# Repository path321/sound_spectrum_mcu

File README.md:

# Sound Analyzer

STM32-powered board for analyzing sound input from MEMS microphones, designed as an open-source, hands-on introduction to DSP on ARM Cortex-M4 processors.

## Table of Contents

1. [About the Project](#about-the-project)
1. [Project Status](#project-status)
1. [Getting Started](#getting-started)
	1. [Getting the Source](#getting-the-source)
	1. [Usage](#usage)
	1. [Versioning](#versioning)
1. [How to get help](#how-to-get-help)
1. [License](#license)

## About the Project

It uses the CMSIS-DSP library to handle computationally intensive tasks, while a companion PyQt-based Python script is used for plotting frequency-domain data data from PCB to host PC. 

The goal is to demonstrate the full pipeline of audio signal acquisition and transformation, from raw time-domain data to frequency-domain analysis

The PCB intentionally exposes additional unused pins, allowing users to extend functionality and experiment beyond the core features

_1kHz sine_

Front                      |  Back
:-------------------------:|:-------------------------:
  |  

**[Back to top](#table-of-contents)**

## Project Status

In progress, working version availabe in `main` branch

Full STM32CubeIDE project is hosted here, with .elf and .bin files ready inside `code/sound_analyzer_v1/Debug` folder

As for python script, both source `plot_graph.py` and executable `plot_graph.exe` are available, with executable tested only for Windows platform

**[Back to top](#table-of-contents)**

## Getting Started

For application usage, no extra programm shall be installed , other than downloading the executable plot_graph.exe

For developer usage, STM32CubeIDE + STM32CubeMX shall be installed, as described [here](https://wiki.st.com/stm32mcu/wiki/STM32StepByStep:Step1_Tools_installation)

In addition, Python >=3.9 shall be installed from [here](https://www.python.org/downloads/), with the following Python libraries also installed :
- Numpy
- PySide6
- pyqtgraph
- Pyserial

PCB files are located on `pcb/` folder, while device files can be found on `code/sound_analyzer_v1/` and plot files on `code/plot_graph/`

### Getting the Source

This project is [hosted on GitHub](https://github.com/path321/sound_spectrum_mcu). You can clone this project directly using this command:

```
https://github.com/path321/sound_spectrum_mcu.git
```

### Usage

1) Connect the board via USB to your host PC. Make sure that no other STM32-based USB is connected to PC

2) Unzip plot_graph.zip Double click on plot_graph.exe

3) If you want to stop the live graph, check on the Button on the top right end of the GUI window

### Versioning

This project uses [Semantic Versioning](http://semver.org/). For a list of available versions, see the [repository tag list](https://github.com/path321/sound_spectrum_mcu/tags).

**[Back to top](#table-of-contents)**

## How to Get Help

Please create a new issue on

```https://github.com/path321/sound_spectrum_mcu/issues```

**[Back to top](#table-of-contents)**

## License

This project is licensed under the MIT License - see [LICENSE.md](LICENSE.md) file for details.

**[Back to top](#table-of-contents)**

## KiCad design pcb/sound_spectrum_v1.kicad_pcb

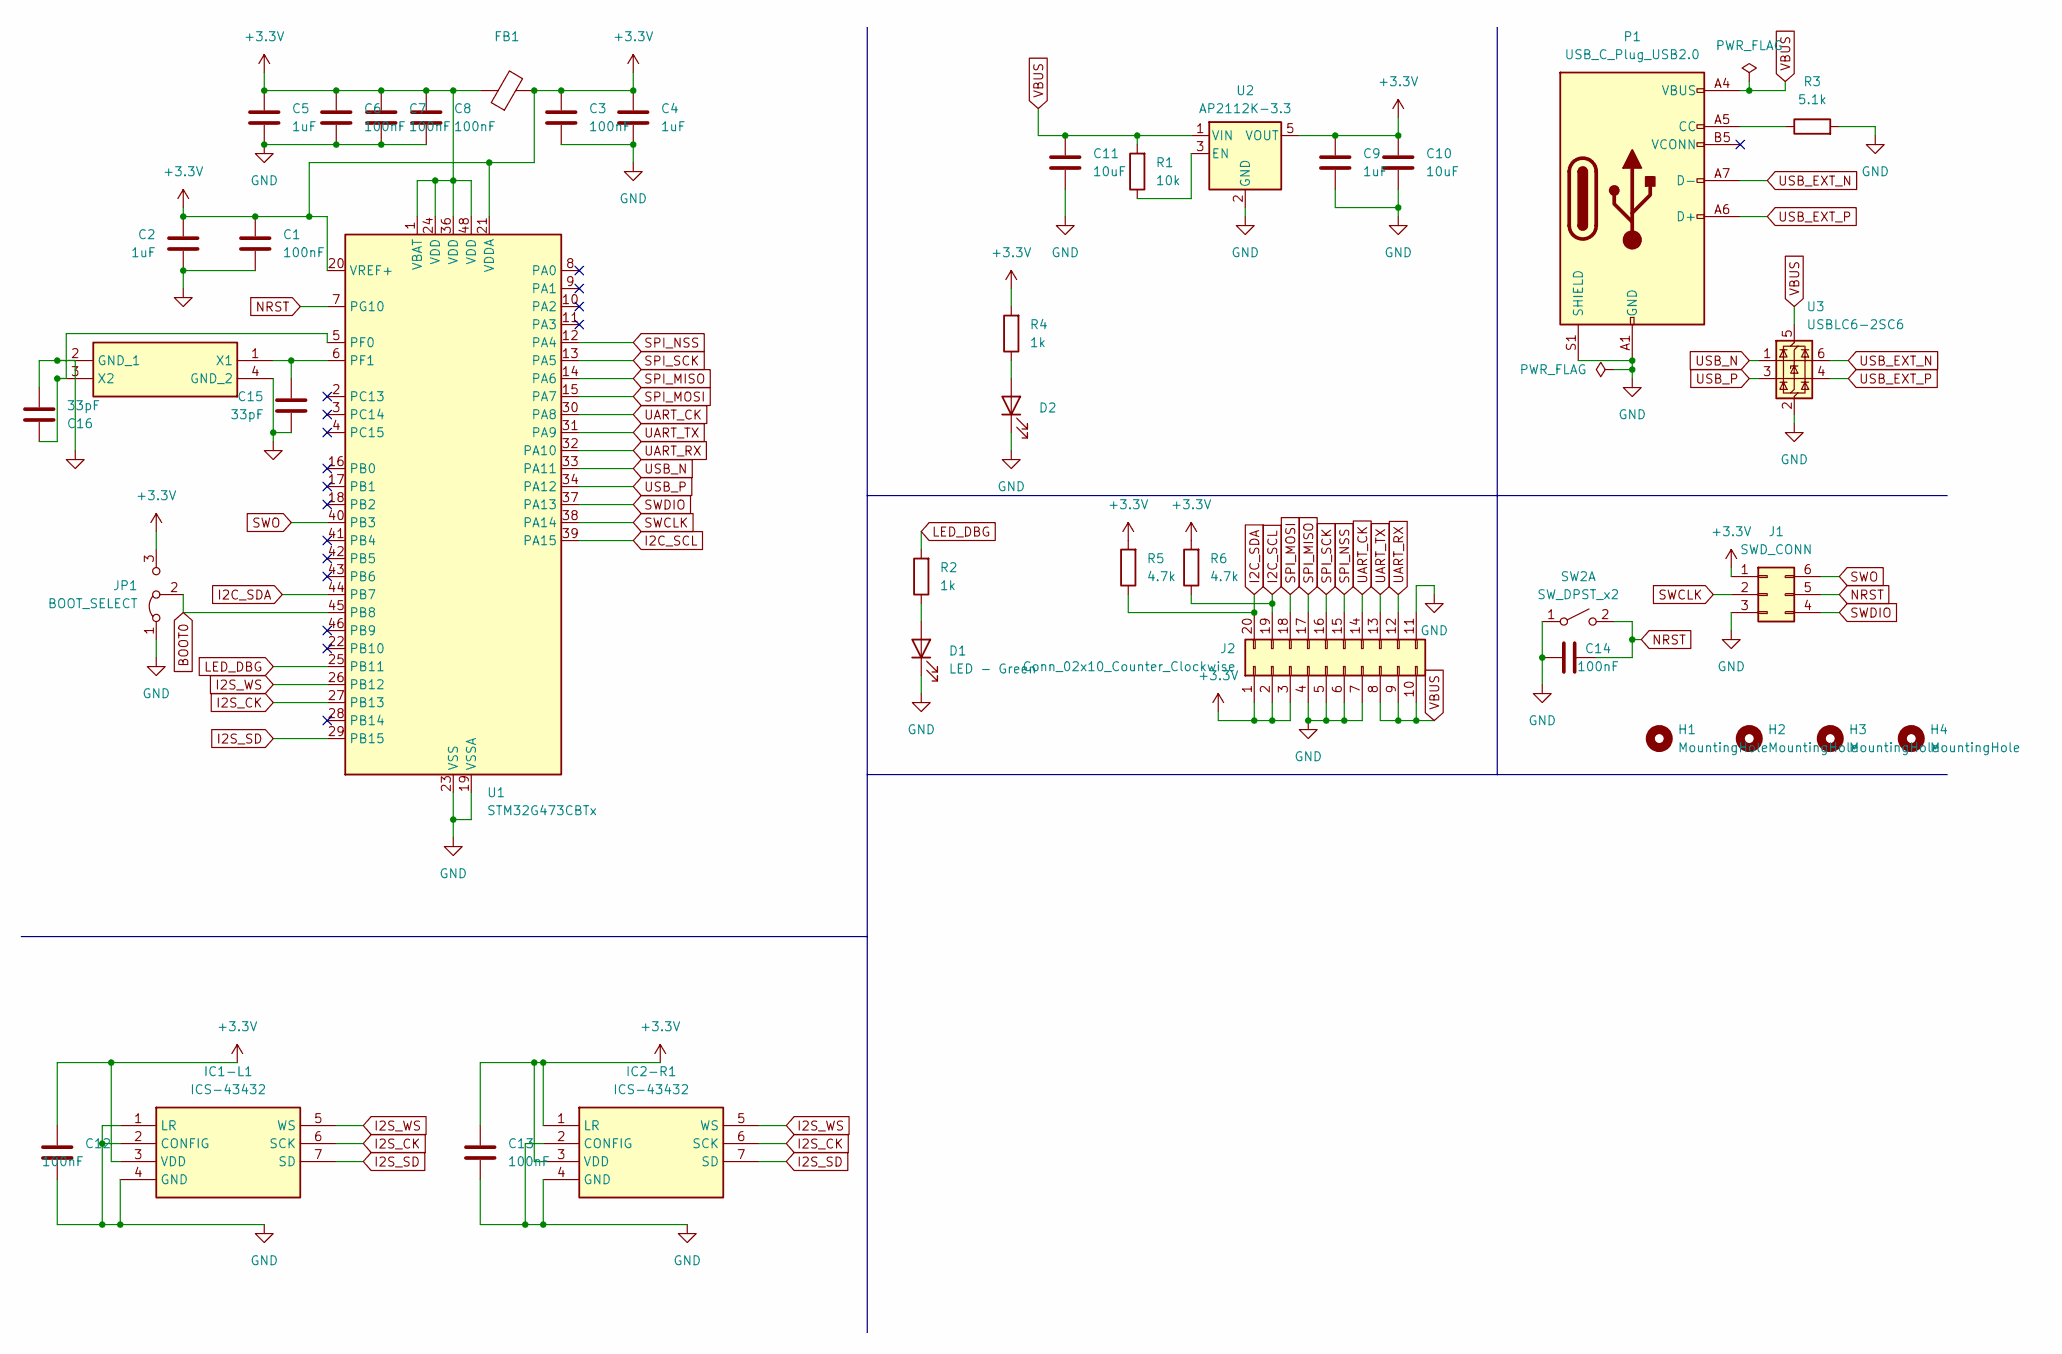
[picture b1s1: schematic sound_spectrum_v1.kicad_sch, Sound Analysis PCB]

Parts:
C1, C3, C6, C7, C8, C12, C13, C14: 100nF; C_0805_2012Metric_Pad1.18x1.45mm_HandSolder; Manufacturer_Part_Number 581-KGM21NR71E104KM
C2, C4, C5, C9: 1uF; C_0805_2012Metric_Pad1.18x1.45mm_HandSolder; Manufacturer_Part_Number 80-C0805C105Z4VAC
C10, C11: 10uF; C_0805_2012Metric_Pad1.18x1.45mm_HandSolder; Manufacturer_Part_Number 81-GRM21BR61C106KE15
C15, C16: 33pF; C_0805_2012Metric_Pad1.18x1.45mm_HandSolder; Manufacturer_Part_Number 80-C0805C105Z4VAC
D1: LED - Green; LED_0805_2012Metric_Pad1.15x1.40mm_HandSolder; Manufacturer_Part_Number C171KGKT
D2: LED - Red; LED_0805_2012Metric_Pad1.15x1.40mm_HandSolder; Manufacturer_Part_Number CMDA5AR7D1S
FB1: L_0805_2012Metric_Pad1.05x1.20mm_HandSolder; Manufacturer_Part_Number ASMPH-0805-4R7M-T
H1, H2, H3, H4: MountingHole; MountingHole_3.2mm_M3_DIN965
IC1-L1, IC2-R1: ICS-43432; ICS43432; Manufacturer_Part_Number ICS-43432; Mouser Part Number 410-ICS-43432
J1: SWD_CONN; PinHeader_2x03_P2.54mm_Vertical; Manufacturer_Part_Number 10129381-906004BLF
J2: Conn_02x10_Counter_Clockwise; PinHeader_2x10_P2.54mm_Vertical; Manufacturer_Part_Number 77313-818-20LF
JP1: BOOT_SELECT; SolderJumper-3_P1.3mm_Bridged2Bar12_Pad1.0x1.5mm
P1: USB_C_Plug_USB2.0; USB_C_Receptacle_GCT_USB4105-xx-A_16P_TopMnt_Horizontal; Manufacturer_Part_Number USB4085-GF-A
R1: 10k; R_0805_2012Metric_Pad1.20x1.40mm_HandSolder; Manufacturer_Part_Number 603-AC0805DR-0710KL
R2, R4: 1k; R_0805_2012Metric_Pad1.20x1.40mm_HandSolder; Manufacturer_Part_Number 603-AA0805FR-071KL
R3: 5.1k; R_0805_2012Metric_Pad1.20x1.40mm_HandSolder; Manufacturer_Part_Number CRCW08055K10JNEA
R5, R6: 4.7k; R_0805_2012Metric_Pad1.20x1.40mm_HandSolder; Manufacturer_Part_Number 603-RC0805FR-074K7L
SW2: SW_DPST_x2; SW_PUSH_6mm; Manufacturer_Part_Number TS04-66-55-BK-100-SMT-TR
U1: STM32G473CBTx; LQFP-48_7x7mm_P0.5mm; Manufacturer_Part_Number STM32G473CBT6
U2: AP2112K-3.3; SOT-23-5; Manufacturer_Part_Number AP2112K-3.3TRG1
U3: USBLC6-2SC6; SOT-23-6; Manufacturer_Part_Number USBLC6-2SC6
Y1: ABMM2-24.000MHZ-E2-T; ABMM2; Mouser Part Number 815-ABMM2-24-E2T

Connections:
+3.3V: C1.1, C2.1, C3.1, C4.1, C5.1, C6.1, C7.1, C8.1, C9.1, C10.1, C12.1, C13.1, FB1.1, FB1.2, IC1-L1.3 (VDD), IC2-R1.1 (LR), IC2-R1.3 (VDD), J1.1, J2.1, J2.2, J2.3, JP1.3 (B), R4.2, R5.2, R6.2, U1.1 (VBAT), U1.20 (VREF+), U1.21 (VDDA), U1.24 (VDD), U1.36 (VDD), U1.48 (VDD), U2.5 (VOUT)
BOOT0: JP1.2 (C), U1.45 (PB8)
GND: C1.2, C2.2, C3.2, C4.2, C5.2, C6.2, C7.2, C8.2, C9.2, C10.2, C11.2, C12.2, C13.2, C14.1, C15.2, C16.2, D1.1 (K), D2.1 (K), IC1-L1.1 (LR), IC1-L1.2 (CONFIG), IC1-L1.4 (GND), IC2-R1.2 (CONFIG), IC2-R1.4 (GND), J1.3, J2.4, J2.5, J2.6, J2.7, J2.11, JP1.1 (A), P1.A1 (GND), P1.A12 (GND), P1.B1 (GND), P1.B12 (GND), P1.S1 (SHIELD), R3.2, SW2.1 (A), U1.19 (VSSA), U1.23 (VSS), U1.35 (VSS), U1.47 (VSS), U2.2 (GND), U3.2 (GND), Y1.2 (GND_1), Y1.4 (GND_2)
I2C_SCL: J2.19, R6.1, U1.39 (PA15)
I2C_SDA: J2.20, R5.1, U1.44 (PB7)
I2S_CK: IC1-L1.6 (SCK), IC2-R1.6 (SCK), U1.27 (PB13)
I2S_SD: IC1-L1.7 (SD), IC2-R1.7 (SD), U1.29 (PB15)
I2S_WS: IC1-L1.5 (WS), IC2-R1.5 (WS), U1.26 (PB12)
LED_DBG: R2.2, U1.25 (PB11)
NRST: C14.2, J1.5, SW2.2 (B), U1.7 (PG10)
unnamed: D1.2 (A), R2.1
unnamed: D2.2 (A), R4.1
unnamed: P1.A5 (CC), R3.1
unnamed: C16.1, U1.5 (PF0), Y1.3 (X2)
unnamed: C15.1, U1.6 (PF1), Y1.1 (X1)
unnamed: R1.1, U2.3 (EN)
SPI_MISO: J2.17, U1.14 (PA6)
SPI_MOSI: J2.18, U1.15 (PA7)
SPI_NSS: J2.15, U1.12 (PA4)
SPI_SCK: J2.16, U1.13 (PA5)
SWCLK: J1.2, U1.38 (PA14)
SWDIO: J1.4, U1.37 (PA13)
SWO: J1.6, U1.40 (PB3)
UART_CK: J2.14, U1.30 (PA8)
UART_RX: J2.12, U1.32 (PA10)
UART_TX: J2.13, U1.31 (PA9)
USB_EXT_N: P1.A7 (D-), U3.6 (I/O1)
USB_EXT_P: P1.A6 (D+), U3.4 (I/O2)
USB_N: U1.33 (PA11), U3.1 (I/O1)
USB_P: U1.34 (PA12), U3.3 (I/O2)
VBUS: C11.1, J2.8, J2.9, J2.10, P1.A4 (VBUS), P1.A9 (VBUS), P1.B4 (VBUS), P1.B9 (VBUS), R1.2, U2.1 (VIN), U3.5 (VBUS)

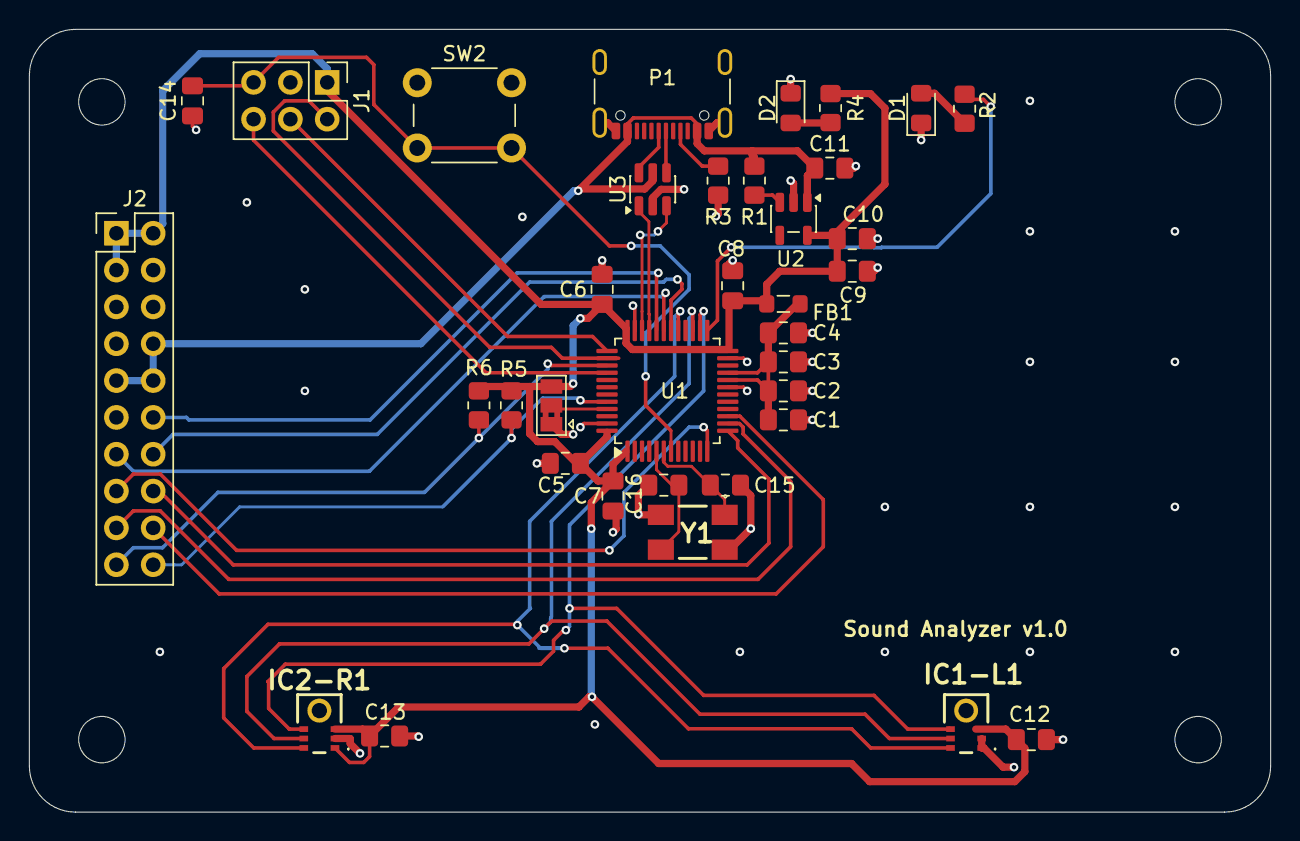
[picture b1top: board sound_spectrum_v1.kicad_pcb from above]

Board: 4 copper layers, 85.6 x 54.0 mm, 40 parts (0 on the bottom side), 31 nets.

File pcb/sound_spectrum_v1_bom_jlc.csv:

Reference,Qty,Value,DNP,Exclude from BOM,Exclude from Board,Footprint,Datasheet,Manufacturer_Part_Number
"C1,C3,C6,C7,C8,C14,C15",7,100nF,,,,Capacitor_SMD:C_0805_2012Metric_Pad1.18x1.45mm_HandSolder,~, 581-KGM21NR71E104KM 
"C2,C4,C5,C9",4,1uF,,,,Capacitor_SMD:C_0805_2012Metric_Pad1.18x1.45mm_HandSolder,~, 80-C0805C105Z4VAC 
"C10,C11",2,10uF,,,,Capacitor_SMD:C_0805_2012Metric_Pad1.18x1.45mm_HandSolder,~, 81-GRM21BR61C106KE15 
D2,1,LED,,,,LED_SMD:LED_0805_2012Metric_Pad1.15x1.40mm_HandSolder,~, CMDA5AR7D1S 
FB1,1,4.7uH,,,,Inductor_SMD:L_0805_2012Metric_Pad1.05x1.20mm_HandSolder,~, ASMPH-0805-4R7M-T 
J1,1,SWD_CONN,,,,Connector_PinHeader_2.54mm:PinHeader_2x03_P2.54mm_Vertical,~, 10129381-906004BLF 
J2,1,Conn_02x10_Counter_Clockwise,,,,Connector_PinHeader_2.54mm:PinHeader_2x10_P2.54mm_Vertical,~,77313-818-20LF
P1,1,USB_C_Plug_USB2.0,,,,Connector_USB:USB_C_Receptacle_GCT_USB4085,https://www.usb.org/sites/default/files/documents/usb_type-c.zip, USB4085-GF-A 
R1,1,10k,,,,Resistor_SMD:R_0805_2012Metric_Pad1.20x1.40mm_HandSolder,~, 603-AC0805DR-0710KL 
R3,1,5.1k,,,,Resistor_SMD:R_0805_2012Metric_Pad1.20x1.40mm_HandSolder,~,CRCW08055K10JNEA
R4,1,1k,,,,Resistor_SMD:R_0805_2012Metric_Pad1.20x1.40mm_HandSolder,~, 603-AA0805FR-071KL 
"R5,R6",2,4.7k,,,,Resistor_SMD:R_0805_2012Metric_Pad1.20x1.40mm_HandSolder,~, 603-RC0805FR-074K7L 
SW2,1,SW_DPST_x2,,,,Button_Switch_THT:SW_PUSH_6mm,~, TS04-66-55-BK-100-SMT-TR 
U1,1,STM32G473CBTx,,,,Package_QFP:LQFP-48_7x7mm_P0.5mm,https://www.st.com/resource/en/datasheet/stm32g473cb.pdf,STM32G473CBT6
U2,1,AP2112K-3.3,,,,Package_TO_SOT_SMD:SOT-23-5,https://www.diodes.com/assets/Datasheets/AP2112.pdf, AP2112K-3.3TRG1 
U3,1,USBLC6-2SC6,,,,Package_TO_SOT_SMD:SOT-23-6,https://www.st.com/resource/en/datasheet/usblc6-2.pdf,USBLC6-2SC6
Y2,1,SG-210STF 48.0000ML5,,,,Oscillator:Oscillator_SMD_SeikoEpson_SG210-4Pin_2.5x2.0mm,https://support.epson.biz/td/api/doc_check.php?mode=dl&lang=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, SG-210STF 48.0000ML5

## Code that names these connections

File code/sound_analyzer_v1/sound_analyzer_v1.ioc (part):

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Mcu.Name=STM32G473C(B-C-E)Tx
Mcu.Package=LQFP48
Mcu.UserName=STM32G473CBTx
PA11.Mode=Device
PA11.Signal=USB_DM
PA12.Mode=Device
PA12.Signal=USB_DP
PA13.Signal=SYS_JTMS-SWDIO
PA14.Signal=SYS_JTCK-SWCLK
PB11.GPIOParameters=GPIO_Label
PB11.GPIO_Label=LED_DBG
PB11.Signal=GPIO_Output
PB12.Mode=Half_Duplex_Master
PB12.Signal=I2S2_WS
PB13.Mode=Half_Duplex_Master
PB13.Signal=I2S2_CK
PB15.GPIOParameters=GPIO_PuPd
PB15.GPIO_PuPd=GPIO_NOPULL
PB15.Mode=Half_Duplex_Master
PB15.Signal=I2S2_SD
PF0-OSC_IN.Mode=HSE-External-Oscillator
PF0-OSC_IN.Signal=RCC_OSC_IN
PF1-OSC_OUT.Mode=HSE-External-Oscillator
PF1-OSC_OUT.Signal=RCC_OSC_OUT
RCC.HSE_VALUE=24000000
RCC.SYSCLKFreq_VALUE=144000000
RCC.SYSCLKSource=RCC_SYSCLKSOURCE_PLLCLK
board=custom

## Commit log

2026-01-15 chore: init commit, with first version of firmware, in progress
    chore: update Readme
2026-02-21 BREAKING CHANGE: change of mcu -> going to f401re, as well as mic -> going to ics43434 ,not working, in progress
2026-03-08 fix: better handling of 24-bit data, in progress
2026-03-08 chore: add some brief docs on functions
2026-03-08 feat: add Hanning window before FFT
2026-03-17 feat: add first version of PCB, in progress
    feat: add first version of python script for bar graph, in progress
    chore: restructure project
2026-03-17 chore: add hanning window as a fixed array
    feat: output .bin file
2026-03-18 feat: form pcb board as credit card-sized
    feat: add esd protection ic to USB singals
    fix: bug with nrst button
    fix: bug with microphone connection in schematic
    chore: added custom rules for board in jlcpcb
2026-03-18 chore: further tracing
2026-03-18 fix: replace ics-43434 with ics-43432 due to part shortage
    feat: make connections to all parts
2026-03-18 chore: move traces around
2026-03-19 feat: add HSE clock
    feat: update schematic
    chore: create gerber files
2026-03-19 chore: generated cpl file
    fix: errors in schematic
2026-03-19 chore: correct silkscreen
2026-03-21 feat: add mounting holes
    chore: change usb c receptor
    chore: align microphones
2026-03-21 chore: minor rerouting
2026-03-21 chore: add extra led
    chore: minor changes
2026-03-21 chore: add text in schematic
2026-04-02 feat: working example of plotting with pyqtgraph, in progress
    chore: minro changes in serial data format from mcu
2026-04-06 BREAKING CHANGE: fw moved from f401re to g473cb
    chore: update Readme
2026-04-06 chore: add todo file
    chore: update readme
2026-04-11 feat: normalize output bins to generate power spectrum
    feat: correct handling of stereo signal
    feat: use specific function for FFT with N -> reduce ~50% output code size
    feat: add hanning window as external file, avoid computing
    feat: change color of plot
    feat: add button for Run/Stop plot, need improving
    chore: renaming of functions for better conceptuality
2026-04-12 chore: code formatting
    chore: add #error guards for specific #define's
2026-04-12 chore: copy input data to another buffer before processing
2026-04-12 fix: bug with memcpy operation
2026-04-12 feat: re-write plot python script, to include PySide6, cleaner code format, interactive button for Run/Stop and symbol for each data point
2026-04-12 feat: add executable file from python script, generated with Nuitka module
    chore: format plot_graph.py with autopep8 module
2026-04-14 feat: remove DC offset before fft & compute dBFS as final result
    feat: check flag for usb transmit completion
    fix: normalize time-domain data to full-scale [-1,1]
    fix: better handling of 24bit-to-32bit format
    fix: more detailed hanning window array
    fix: use N=1024 instead of 2048 -> more stable operation
    feat: add axis labels in plot
2026-04-16 feat: try a-weighting correction
2026-04-18 feat: add flattop & rectangular window as options
    feat: add flexible normalization factor, depending on selected window
    feat: add led flashing pattern in error handler
    chore: change the range of y axis to conform to dbspl in plot_graph
    chore: add another function for translating freq magnitude values to dB
2026-04-18 chore: change basic gitignore file
2026-04-21 chore: updated readme, added images
    chore: created nuitka .exe , in progress
2026-04-21 chore: update readme
    chore: updated .exe for plotting
2026-04-21 chore: update readme
    chore: change images to .jpg
    chore: put .exe into zip
2026-06-01 chore: refactor mcu code with encapsulation
    fix: bug with python serial
2026-06-02 chore: update plot_graph.exe inside zip
